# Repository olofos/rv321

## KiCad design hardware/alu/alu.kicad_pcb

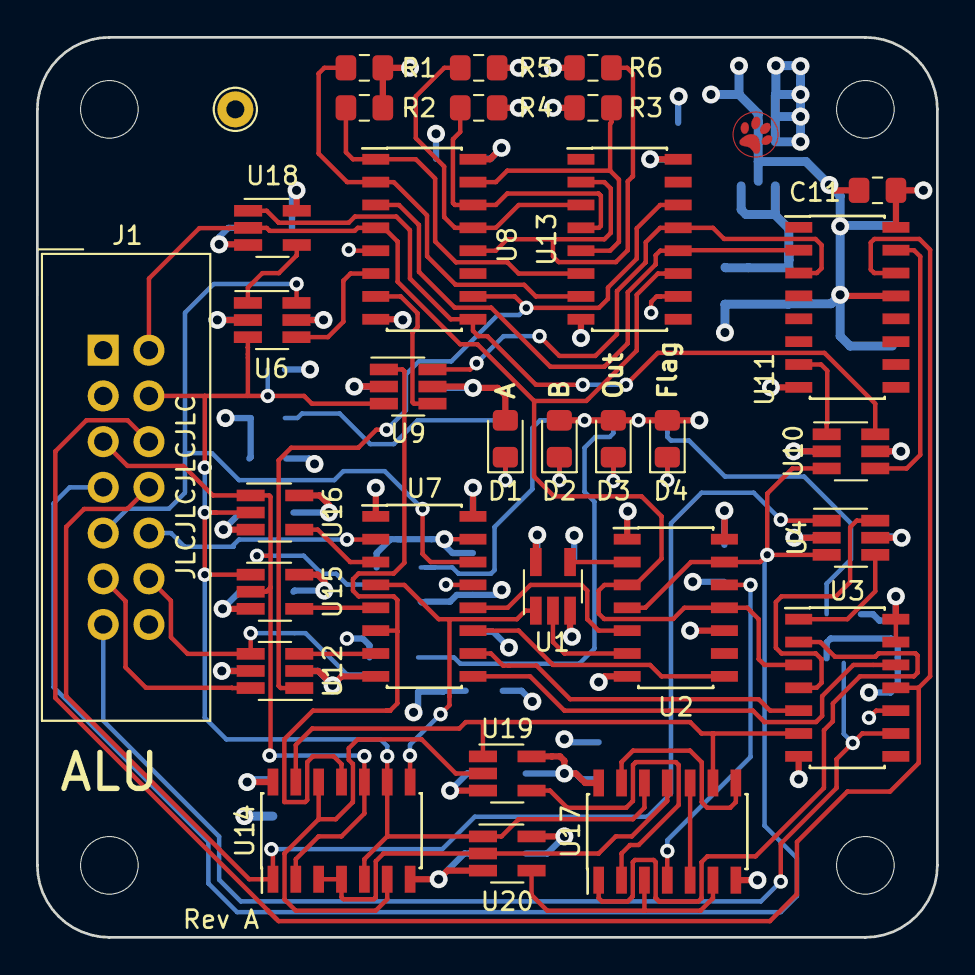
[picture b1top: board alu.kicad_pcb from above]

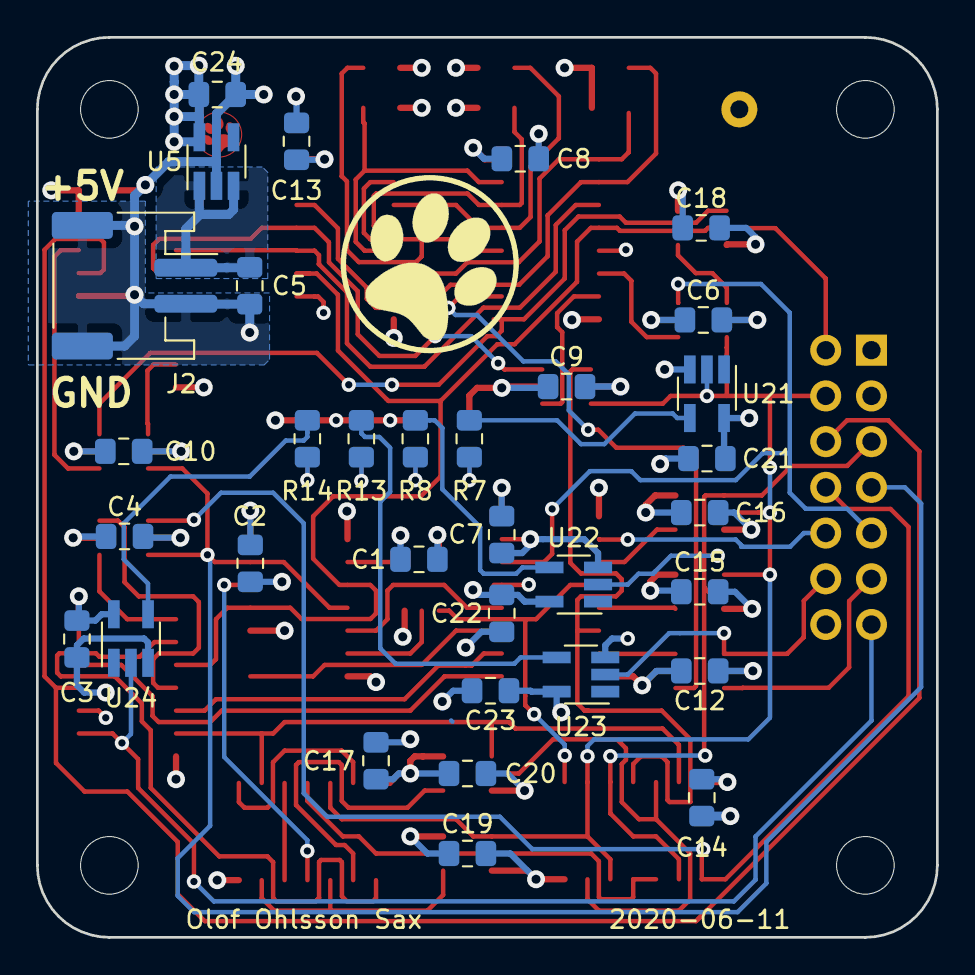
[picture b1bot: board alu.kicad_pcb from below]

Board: 4 copper layers, 50.0 x 50.0 mm, 69 parts (33 on the bottom side), 59 nets.

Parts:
C1, C2, C3, C4, C6, C7, C8, C9, C10, C11, C12, C13, C14, C15, C16, C17, C18, C19, C20, C21, C22, C23: 100n; C_0805_2012Metric_Pad1.15x1.40mm_HandSolder
C5, C24: 1u; C_0805_2012Metric_Pad1.15x1.40mm_HandSolder
D1, D2, D3, D4: LED; LED_0805_2012Metric_Pad1.15x1.40mm_HandSolder
H1, H2, H3, H4: MountingHole; MountingHole_3.2mm_M3
J1: Conn_ALU; IDC-Header_2x07_P2.54mm_Vertical
J2: Conn_Power; JST_PH_S2B-PH-SM4-TB_1x02-1MP_P2.00mm_Horizontal
R1, R2, R3, R4, R5, R6: 10k; R_0805_2012Metric_Pad1.15x1.40mm_HandSolder
R7, R8, R13, R14: 330; R_0805_2012Metric_Pad1.15x1.40mm_HandSolder
TP1: TestPoint; TestPoint_THTPad_D2.0mm_Drill1.0mm
U1: 74LVC1G02; SOT-23-5_HandSoldering
U2, U3: 74HC74; SOIC-14_3.9x8.7mm_P1.27mm
U4: 74LVC1G19; SOT-23-6_Handsoldering
U5: MIC5504-3.3YM5; SOT-23-5_HandSoldering
U6: 74LVC1G175; SOT-23-6_Handsoldering
U7: 74HC253; SOIC-16_3.9x9.9mm_P1.27mm
U8: HEF4557B; SOIC-16_3.9x9.9mm_P1.27mm
U9, U12: 74LVC1G157; SOT-23-6_Handsoldering
U10: 74AUC2G04; SOT-23-6_Handsoldering
U11: 74HC4017; SOIC-16_3.9x9.9mm_P1.27mm
U13: 74HC595; SOIC-16_3.9x9.9mm_P1.27mm
U14: 74HC86; SOIC-14_3.9x8.7mm_P1.27mm
U15: 74LVC1G32; SOT-23-5_HandSoldering
U16, U18, U19, U20: 74LVC1G08; SOT-23-5_HandSoldering
U17: 74HC02; SOIC-14_3.9x8.7mm_P1.27mm
U21, U22, U23, U24: 74LVC1G04; SOT-23-5_HandSoldering

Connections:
/(A+B)&C: U17.2, U19.4
/A&~B: U17.3, U17.6, U20.4
/A+B: U14.6, U14.12, U19.2
/ALU_AUX: J1.6, U3.11, U11.14
/ALU_S0: J1.9, U6.6, U7.14
/ALU_S1: J1.10, U7.2
/ALU_S2: J1.11, U12.6
/BUS_CLK: J1.2, U2.3, U2.11, U3.3, U8.4, U13.11, U18.2
/B_OR_~B: U14.3, U14.4, U17.11, U20.2
/C_TO_NEG: U17.5, U17.10
/DAH: D1.1, R7.2
/DAL: R7.1, U21.4
/DBH: D2.1, R8.2
/DBL: R8.1, U22.4
/DFH: D4.1, R14.2
/DFL: R14.1, U24.4
/DOH: D3.1, R13.2
/DOL: R13.1, U23.4
/EQUAL: U2.5, U7.12
/EQ_FF_D: U1.4, U2.2
/EQ_FF_~Q: U1.2, U2.6
/FLAG: U3.12, U7.9
/IN_A: J1.4, U6.3, U9.3, U14.5, U14.9, U15.1, U16.2, U17.12, U20.1, U21.2
/IN_B: J1.5, U14.2, U14.10, U15.2, U16.1, U22.2
/IN_C: U3.6, U14.13, U17.9, U19.1
/IN_N: J1.8, U4.1, U14.1
/L1: R1.2, U8.2, U13.7
/L2: R2.2, U8.1, U13.6
/L4: R3.2, U8.15, U13.5
/L8: R4.1, U8.14, U13.4
/L16: R5.2, U8.13, U13.3
/L32: R6.1, U8.12, U13.2
/LT: U2.8, U7.11
/LTU: U3.5, U7.10
/OUT: J1.12, U12.4, U23.2
/OUT_AND: U7.3, U16.4
/OUT_BIN: U7.7, U12.3
/OUT_FLAG: J1.13, U3.9, U24.2
/OUT_OR: U7.5, U15.4
/OUT_SHIFT: U8.10, U12.1, U13.14
/OUT_SUM: U7.6, U9.1, U14.11
/OUT_XOR: U1.1, U7.4, U14.8
/SH_4017_MR: U10.4, U11.15
/SH_IN: U8.7, U9.4
/SH_LOADLEN: U9.6, U11.3, U13.13
/SH_OUTPUT: U10.1, U11.7
/SH_RESET: U8.3, U11.2, U13.12
/SH_S_FF_C: U6.1, U18.4
/SH_S_FF_Q: U6.4, U8.6
/V_IN: C5.1, J2.1, U5.1, U5.3
/~ALU_RESET: J1.7, U2.4, U2.13, U4.3, U10.3
/~A&B: U17.8, U17.13
/~C_FF_~R: U3.1, U4.4
/~C_FF_~S: U3.4, U4.6
/~OUT_C: U3.2, U17.1
/~OUT_NEG: U2.12, U17.4
/~SH_OUTPUT: U8.9, U10.6, U18.1
GND: C1.2, C2.2, C3.2, C4.2, C5.2, C6.2, C7.2, C8.2, C9.2, C10.2, C11.2, C12.2, C13.2, C14.2, C15.2, C16.2, C17.2, C18.2, C19.2, C20.2, C21.2, C22.2, C23.2, C24.2, J1.1, J1.3, J1.14, J2.2, J2.MP, R4.2, R6.2, TP1.1, U1.3, U2.7, U3.7, U4.2, U5.2, U6.2, U7.1, U7.8, U7.13, U7.15, U8.5, U8.8, U9.2, U10.2, U11.8, U11.13, U12.2, U13.8, U14.7, U15.3, U16.3, U17.7, U18.3, U19.3, U20.3, U21.3, U22.3, U23.3, U24.3
VCC: C1.1, C2.1, C3.1, C4.1, C6.1, C7.1, C8.1, C9.1, C10.1, C11.1, C12.1, C13.1, C14.1, C15.1, C16.1, C17.1, C18.1, C19.1, C20.1, C21.1, C22.1, C23.1, C24.1, D1.2, D2.2, D3.2, D4.2, R1.1, R2.1, R3.1, R5.1, U1.5, U2.1, U2.10, U2.14, U3.10, U3.13, U3.14, U4.5, U5.5, U6.5, U7.16, U8.16, U9.5, U10.5, U11.16, U12.5, U13.10, U13.16, U14.14, U15.5, U16.5, U17.14, U18.5, U19.5, U20.5, U21.5, U22.5, U23.5, U24.5
